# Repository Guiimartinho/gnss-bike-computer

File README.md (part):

<div align="center">

# GNSS Bike Computer

**Computador de bordo para ciclismo com GPS: segmentos do Strava em tempo real, percursos, altimetria por fusão de sensores e sensores sem fio. Portado do stravaV10 para Zephyr, do nRF52840 da myStravaB V3 para o nRF54LM20A de uma placa própria com GNSS de banda dupla e painel solar.**

</div>

O projeto leva para o nRF Connect SDK o **stravaV10**, firmware aberto de Vincent Gollé para a placa **myStravaB V3**: um aparelho em retrato com LCD de memória Sharp, GNSS MediaTek, barômetro, acelerômetro, medidor de bateria, microSD e rádio BLE + ANT+. O código original fica em [`legacy/`](legacy/) como referência de comportamento; o port em C puro sobre Zephyr fica em [`zephyr_app/`](zephyr_app/) e compila para o nRF54LM20 DK, para a placa do projeto (`gnssbike/nrf54lm20a/cpuapp`) e ainda para o nRF52840-DK, que saiu de uso. A próxima placa é própria, com o nRF54LM20A, GNSS de banda dupla, tela colorida e painéis solares na caixa que estendem a autonomia, sem sustentar o aparelho sozinhos; a especificação e a avaliação dos componentes estão em [`docs/`](docs/README.md).

> [!WARNING]
> O port **compila e passa nos testes de host, mas nunca rodou em placa nem nos DKs**. Segmentos, percursos, sensores BLE e ANT+, log no SD e a interface do legacy ainda não funcionam de ponta a ponta. A placa nova está roteada e com os arquivos de fábrica prontos, mas não foi fabricada: nenhum componente foi comprado nem medido. O estado de cada área está em [docs/10-status-do-port.md](docs/10-status-do-port.md).

## Índice

- [Visão geral](#visão-geral)
- [Placa nova](#placa-nova)
- [Funcionalidades](#funcionalidades)
- [Início rápido](#início-rápido)
- [Estrutura](#estrutura)
- [Documentação](#documentação)
- [Estado e próximos passos](#estado-e-próximos-passos)
- [Créditos e licenças](#créditos-e-licenças)

## Visão geral

```mermaid
flowchart LR
    subgraph DEV["myStravaB V3 · nRF52840"]
        MODEL["modelo<br/>altitude, potência,<br/>segmentos, percurso"]
        VUE["interface<br/>LCD LS027 + 3 botões"]
        LOG["log no microSD"]
    end
    GNSS["GNSS M10578-A3"] -->|NMEA| MODEL
    SENS["BME280 · FXOS8700 · STC3100"] -->|I2C| MODEL
    SENSORS["frequência cardíaca, cadência,<br/>potência, rolo"] -->|"ANT+ / BLE"| MODEL
    PHONE["celular<br/>Komoot, LNS"] -->|BLE| MODEL
    MODEL --> VUE
    MODEL --> LOG
    PC["PC"] <-->|"USB / stravaAP"| DEV
```

## Placa nova

<div align="center">

*A placa `gnssbike` roteada, 34 × 95 mm em 4 camadas, como sai na montagem da JDI, gerada por programa a partir dos documentos de `hardware_gnssbike/`.*

</div>

| | |
|---|---|
|  |  |
| *Frente: os dois conectores da tela, na borda esquerda: o `J402`, da luz da JDI (5 vias), e o `J401`, do sinal (10 vias), que serve às duas telas* | *Verso: o buzzer, o `J103` do painel solar e as ilhas do `J403`, que recebe a luz do Azumo na montagem da Sharp* |

| | |
|---|---|
|  |  |
| *A caixa proposta, 64 × 106 × 18,2 mm desde 2026-10-19, medida por um dry run próprio* | *Explodida: tampa com o display, teclas, módulos solares, porta do USB-C* |

A caixa foi desenhada em volta da placa real ([`hardware_gnssbike/caixa/`](hardware_gnssbike/caixa/README.md), decisões em [`hardware_gnssbike/04`](hardware_gnssbike/04-pcb-e-caixa.md#a-placa-de-hoje-dentro-da-caixa-do-conceito)); a placa, dimensionada pelo circuito e **não** pela caixa, tem 34 × 95 mm em 4 camadas, 6 módulos solares na faceta e nos chanfros laterais da caixa. A escolha de cada componente, com os números dos datasheets, está em [docs/15-avaliacao-componentes.md](docs/15-avaliacao-componentes.md); a lista de compras, validada peça a peça, em [docs/19-lista-de-compras.md](docs/19-lista-de-compras.md).

A placa existe como **arquivo de CAD**, gerado por programa e **roteado por
inteiro** em 2026-10-19: 138 componentes na montagem da JDI (146 na da
Sharp), 118 redes, 2.683 trechos de trilha e 769 vias. O DRC completo dá 0
itens desconectados e 0 erros, e as regras que as fichas dos componentes e a
IPC-2221B impõem, medidas uma a uma, dão 35 cumpridas, 2 com desvio aceito
pelo dono e conferência de bancada, e nenhuma violada
([dry run de 2026-10-19](hardware_gnssbike/09-dry-run-da-pcb.md#resultado-de-2026-10-19-com-o-roteamento-fechado)).
Os arquivos de fábrica da JLCPCB e as listas de compra da Mouser, da LCSC e
da DigiKey saem por script ([19](docs/19-lista-de-compras.md#compra-na-mouser)).
A caixa existe como proposta em volta da placa, medida por um dry run
próprio (12 regras cumpridas, nenhuma violada, 1 ainda sem medida). Nenhuma
placa foi fabricada, nada foi impresso e nenhum componente passou por
bancada. O esquemático, a placa, a caixa e como se confere cada etapa estão
em [hardware_gnssbike/](hardware_gnssbike/README.md).

```mermaid
flowchart LR
    MCU["MinewSemi ME54BS13<br/>nRF54LM20A, BLE e ANT+"]
    GNSS2["u-blox MAX-F10S<br/>L1 + L5, 46,8 mW"] -->|UART| MCU
    LCD2["JDI LPM027M128C de 8 cores, com luz,<br/>ou Sharp com a luz do Azumo"] ---|"SPI pelo J401"| MCU
    PWR["nPM1300, ADP5091, MAX17262<br/>USB-C e painel solar"] -.->|I2C| MCU
    SENS2["BMP585, BMI270,<br/>MMC5603NJ, OPT3001"] -->|I2C| MCU
    MEM["flash MX25R6435F<br/>8 MB, soldada"] ---|SPI| MCU
```

| Bloco | Escolha | Por quê |
|---|---|---|
| Carga | nPM1300 no USB-C, ADP5091 no painel, MAX17262 na célula | o painel carrega com o aparelho desligado e corte térmico próprio; o USB bloqueia a carga solar no hardware |
| GNSS | u-blox MAX-F10S, banda dupla L1 + L5, com o MAX-M10N-10B (só L1) no mesmo footprint | 1 m de CEP contra 1,5 m, e o código do L5 contra o multipercurso de prédio e mata. Custa autonomia: o aparelho gasta cerca de 58 mW e dura cerca de 115 h sem sol, e o painel devolve de 23 a 46 min por hora de sol em vez de cobrir o consumo. Com o M10N em LEAP seriam cerca de 21 mW e 310 h (estimativas) |
| Tela | JDI LPM027M128C de 8 cores, **com luz frontal integrada** (escolha do dono em 2026-09-23); de reserva, a Sharp LS027B7DH01A, nua ou como o módulo Azumo 11103-06, que traz a luz | as duas entram pelo mesmo conector de sinal, o `J401` (10 vias, contato dos dois lados), na borda esquerda da placa, e a luz tem conector próprio: o `J402` (5 vias), ao lado dele, na JDI, e o `J403` (4 vias, no verso) no Azumo. A montagem da Sharp leva também o boost de 5 V. O firmware atende as duas pelo mesmo driver, em retrato, com um tema para cada |
| USB e armazenamento | USB-C HRO TYPE-C-31-M-12 e flash MX25R6435F soldada | caixa sem tampas e sem cartão solto na vibração |

## Funcionalidades

| Funcionalidade | Legacy | Port |
|---|---|---|
| Segmentos do Strava com avanço contra o recorde | sim | lógica portada, sem carga de dados |
| Percurso com mapa e zoom | sim | parcial, não ligado |
| Altitude por Kalman de 3 estados, subida, inclinação | sim | portado com diferenças |
| Potência estimada | sim | fórmula diferente |
| Sensores ANT+ (FC, velocidade e cadência, rolo FE-C) | sim | a pilha do add-on `sdk-ant` compila com o NCS v3.3.0 (`ANT=1`) e o firmware abre canal escravo; **nenhum canal abre de fato**, porque os perfis ficam fora do repositório e `GNSS_ANT_*_DEV_TYPE` valem 0 |
| BLE (potência, posição do celular, Komoot) | sim | parcial |
| Zonas de potência, suffer score, variabilidade da FC | sim | portados e testados, sem dados reais |
| Log no microSD e download pelo PC | sim | FatFs de verdade, gravado pelo serviço de armazenamento; não testado com cartão |
| USB serial e mass storage | sim | serviço `usb` no build (CDC dos comandos e o disco do ciclista); não testada com cabo |
| Telas em retrato, menu, notificações, botões | sim | LVGL no firmware com driver próprio da tela, 44 quadros testados no PC; nunca vistos num painel |

## Início rápido

**Pré-requisitos** (Windows): nRF Connect SDK v3.3.0 em `C:\ncs` com o toolchain `936afb6332`, SEGGER J-Link, nRF54LM20 DK (o nRF52840-DK ainda compila, mas saiu de uso). Para o ANT, o add-on `sdk-ant` em `C:\ncs\sdk-ant`, depois de aceitar o acordo ANT+ ([07](docs/07-radio-ant-ble.md#ant-no-ncs-v330)). Para os testes de host: MinGW-w64 GCC, CMake e Ninja. Detalhes em [docs/03-ambiente-build.md](docs/03-ambiente-build.md).

Código: [github.com/Guiimartinho/gnss-bike-computer](https://github.com/Guiimartinho/gnss-bike-computer) (`git clone https://github.com/Guiimartinho/gnss-bike-computer.git`).

```sh
# Git Bash, na raiz do repositório
bash tools/fw/fw.sh build          # compila o zephyr_app (sysbuild) para o nRF54LM20 DK
bash tools/fw/fw.sh flash          # grava no DK pelo J-Link
BOARD=gnssbike/nrf54lm20a/cpuapp BUILD_DIR=zephyr_app/build_custom bash tools/fw/fw.sh build   # a placa do projeto
ANT=1 bash tools/fw/fw.sh build pristine   # com a pilha ANT do sdk-ant
bash tools/fw/host_tests.sh        # 53 conjuntos, 714 casos
python tools/ui/render_screens.py  # desenha os 44 quadros no PC (docs/telas)
python tools/docs/mermaid_check.py # valida os diagramas da documentação
```

No `cmd` ou com duplo clique: `build.bat`, `flash.bat`, `recover.bat`, `serial.bat COMx`.

O CI (`.github/workflows/ci.yml`) está **desligado**: só roda à mão, pela aba Actions do GitHub ([detalhes](docs/03-ambiente-build.md#ci)).

## Estrutura

```mermaid
flowchart TB
    ROOT["gnss_bike_computer/"]
    ROOT --> ZA["zephyr_app/<br/>port Zephyr: src, include, boards, modules, tests/host"]
    ROOT --> LEG["legacy/<br/>stravaV10 original (referência)"]
    ROOT --> LIB["libraries/<br/>bibliotecas do legacy"]
    ROOT --> TOOLS["tools/<br/>fw e docs do projeto · TDD, zpm, MMD, jumper do legacy"]
    ROOT --> HW["hardware/<br/>Eagle da myStravaB V3 (Gerbers da V2)"]
    ROOT --> HWN["hardware_gnssbike/<br/>a placa nova: docs 01 a 12, cad (KiCad e geradores),<br/>esquematico, placa, caixa (PDF, STL, dry run), datasheets,<br/>fabricacao (gerada, fora do git)"]
    ROOT --> DOCS["docs/<br/>documentação numerada, img (telas, hardware), historico"]
    ROOT --> AI["CLAUDE.md · AGENTS.md · .claude/skills/ · .claude/contexto/"]
    ROOT --> BAT["build.bat · flash.bat · recover.bat · serial.bat"]
```

## Documentação

| Documento | Assunto |
|---|---|
| [01 · Visão geral](docs/01-visao-geral.md) | produto, modos, legacy e port |
| [02 · Hardware](docs/02-hardware.md) | placa, pinagem, alimentação, alvo no DK |
| [03 · Ambiente e build](docs/03-ambiente-build.md) | NCS v3.3.0, scripts, gravação, problemas conhecidos |
| [04 · Arquitetura do legacy](docs/04-arquitetura-legacy.md) | tasks, modos, glossário |
| [05 · Arquitetura do port](docs/05-arquitetura-zephyr.md) | threads, fluxo de dados, pilhas, devicetree |
| [06 · Algoritmos](docs/06-algoritmos.md) | fórmulas e constantes, legacy × port |
| [07 · Rádio](docs/07-radio-ant-ble.md) | ANT+, BLE, stravaAP, Komoot |
| [08 · Interface](docs/08-interface.md) | telas, menus, botões |
| [09 · Armazenamento e USB](docs/09-armazenamento-usb.md) | formatos de arquivo, SD, USB |
| [10 · Status do port](docs/10-status-do-port.md) | matriz, correções, defeitos, roteiro, decisões |
| [11 · Qualidade e MISRA](docs/11-qualidade-misra.md) | regras e análise estática |
| [12 · Ferramentas e testes](docs/12-ferramentas-testes.md) | testes de host, simulador do legacy, licenças |
| [13 · Placa nova](docs/13-placa-nova.md) | proposta de hardware da placa própria |
| [14 · Hardware da placa nova](docs/14-hardware-placa-nova.md) | especificação técnica: alimentação, lista de materiais, pinos, PCB |
| [15 · Avaliação dos componentes](docs/15-avaliacao-componentes.md) | escolha de cada componente da placa nova, com números de datasheet |
| [16 · Arquitetura do firmware](docs/16-arquitetura-firmware.md) | arquitetura-alvo e máquinas de estado para a placa nova |
| [17 · Dispositivos BLE e ANT+](docs/17-dispositivos-ble-ant.md) | catálogo de sensores e acessórios, prioridades e limites do rádio |
| [18 · Interface e telas](docs/18-interface-telas.md) | interface LVGL da placa nova: todas as telas, desenhadas e testadas no PC, em 8 cores e em preto e branco |
| [19 · Lista de compras](docs/19-lista-de-compras.md) | peças validadas em duas passagens, trocas, correções de integração, e o pedido dividido entre Mouser, LCSC e DigiKey |
| [Hardware da placa nova](hardware_gnssbike/README.md) | o esquemático folha a folha, os cálculos, a lista de nós, a placa e a caixa, os conectores, o layout e os dois dry runs; o CAD em [`cad/`](hardware_gnssbike/cad/README.md), a caixa em [`caixa/`](hardware_gnssbike/caixa/README.md), os PDF em [`esquematico/`](hardware_gnssbike/esquematico/) e [`placa/`](hardware_gnssbike/placa/) |
| [CHANGELOG](CHANGELOG.md) | histórico de mudanças |

## Estado e próximos passos

- **Feito em 2026-09-18:** build no NCS v3.3.0 com sysbuild; correção de 13 defeitos críticos (estouro de pilha no Kalman, GPS e modelo dentro de ISR, corrupção de memória no log, botões e pinos do GPS invertidos, conflitos de pinos com o DK); testes de host; documentação e contexto para assistentes de IA.
- **Fase 1 do roteiro:** a base da arquitetura nova (serviços com thread própria, eventos no zbus, máquinas de sistema e de modo no SMF, watchdog por serviço, desligamento automático do legacy), feita em 2026-09-19.
- **Novos alvos e rádio:** o port compila para o nRF54LM20 DK, e a pilha ANT do add-on `sdk-ant` v2.1.1 compila sobre o NCS v3.3.0 nos dois DKs (`ANT=1`); nada disso foi testado em placa.
- **Interface:** os 44 quadros em LVGL, testadas no PC, rodam no firmware desde 2026-09-19 com um driver próprio da tela (JDI LPM027M128B em 8 cores ou Sharp em preto e branco, em retrato), teclas com toque longo e a máquina da luz; nunca vistas num painel.
- **Placa nova:** desenho do aparelho, especificação ([14](docs/14-hardware-placa-nova.md)) e avaliação dos componentes ([15](docs/15-avaliacao-componentes.md)). Os testes de bancada da carga dupla, do GNSS (C/N0 por banda e isolamento da antena contra o rádio de 2,4 GHz), da coexistência dos rádios e do display ficam para o protótipo.
- **Hardware da placa nova (2026-09-23 a 10-20):** o esquemático em sete folhas, revisado em 2026-10-18; a placa de 34 × 95 mm colocada por programa e roteada por inteiro em 2026-10-19, que aceita a JDI ou a Sharp; o desenho de montagem, o manual e o chicote solar; os dry runs da placa (as regras das fichas e da IPC-2221 medidas no arquivo) e da caixa (a caixa medida contra a placa); a caixa de 64 × 106 × 18,2 com STL para a primeira prova; os arquivos de fábrica da JLCPCB e as listas de compra. Nada fabricado, nada impresso, nenhum componente na bancada; o que falta antes de mandar fabricar está em [`hardware_gnssbike/README.md`](hardware_gnssbike/README.md#antes-de-mandar-fabricar).
- **Decidido:** ANT+ e BLE juntos (os equipamentos externos falam ANT+) e placa própria com o nRF54LM20A. Decisões e pendências em [docs/10-status-do-port.md](docs/10-status-do-port.md#decisões-do-dono).
- **Próximo:** as confirmações que faltam antes de mandar fabricar (o mapa de pads do módulo num exemplar real, o domínio de tensão do nPM1300, a pinagem da bateria), a compra das peças e a primeira prova impressa da caixa; depois, os testes de bancada da placa nova (carga dupla, isolamento entre as antenas, o display sobre a antena GNSS); no firmware, fidelidade dos algoritmos, armazenamento, rádio e interface. Roteiro em [docs/10-status-do-port.md](docs/10-status-do-port.md#roteiro).

## Créditos e licenças

- **stravaV10** e **myStravaB**: Vincent Gollé ([vincent290587/stravaV10](https://github.com/vincent290587/stravaV10)), licenciado sob **Creative Commons Atribuição-NãoComercial 4.0 (CC BY-NC 4.0)**. O port deriva desse código; ver [`legacy/README.md`](legacy/README.md).
- Bibliotecas de terceiros em `libraries/` e `tools/` mantêm suas licenças (BSD, LGPL-2.1, GPL-2.0, Nordic, SEGGER): tabela em [docs/12-ferramentas-testes.md](docs/12-ferramentas-testes.md#bibliotecas-e-licenças).
- O add-on `sdk-ant` e o material ANT+ não fazem parte do repositório: o ANT+ Adopter Agreement proíbe redistribuir ([07](docs/07-radio-ant-ble.md#decisão-ant-e-ble)).
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
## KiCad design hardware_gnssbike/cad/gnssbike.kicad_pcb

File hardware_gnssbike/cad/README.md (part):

# Projeto KiCad da placa

Este diretório é o projeto de CAD do GNSS Bike Computer: **esquemático
hierárquico em sete folhas** e **placa com as 166 peças posicionadas e
roteadas**, em KiCad 8, gerados a partir dos documentos de
[`hardware_gnssbike/`](../README.md) e conferidos contra eles por programa.

> [!WARNING]
> **Nada aqui foi fabricado, montado ou medido.** Não existe placa, não existe
> protótipo e nenhum número desta página saiu de bancada. O roteamento é feito
> por programa e está **completo desde 2026-10-19** (0 itens desconectados e 0
> erros no DRC completo), com rotina própria para as linhas de RF; nenhuma
> placa de verdade o conferiu.

## O que abrir

| Arquivo | O que é |
|---|---|
| `gnssbike.kicad_pro` | o projeto; **abra este** no KiCad |
| `gnssbike.kicad_sch` | folha raiz: o diagrama de blocos |
| `folha1-energia.kicad_sch` … `folha6-interface.kicad_sch` | as seis folhas |
| `gnssbike.kicad_pcb` | a placa |
| `gnssbike.kicad_dru` | as duas regras locais de folga |
| `zonas.dxf`, `contorno-r3.dxf`, `contorno-r4.dxf` | as zonas e o contorno da placa em DXF, gerados pelo `make_dxf.py` (entradas da placa, não saídas) |

O que se **lê** sai daqui para as pastas do assunto (reorganização de 2026-09-26): o esquemático em PDF para [`../esquematico/`](../esquematico/), a placa em PDF e SVG e o desenho de montagem para [`../placa/`](../placa/), a proposta de caixa (PDF, STL e os dois scripts dela) para [`../caixa/`](../caixa/README.md), e as vistas 3D da placa e da caixa para [`../../docs/img/hardware/`](../../docs/img/hardware/). A tabela de [`../README.md`](../README.md#o-cad-e-o-que-sai-dele) lista cada arquivo. O `gnssbike.glb` que o `kicad-cli` exporta fica aqui e fora do git (45 MB, regenerado quando a placa muda).

## O esquemático

```mermaid
flowchart TB
    RAIZ["folha raiz · A3<br/>diagrama de blocos<br/>as linhas entre as folhas"]
    RAIZ --> F1["1 Energia · A3<br/>79 posicoes em 6 blocos"]
    RAIZ --> F2["2 MCU e depuracao · A4<br/>14 posicoes em 2 blocos"]
    RAIZ --> F3["3 GNSS · A4<br/>13 posicoes em 2 blocos"]
    RAIZ --> F4["4 Display e luz · A4<br/>15 posicoes em 2 blocos"]
    RAIZ --> F5["5 Memoria e sensores · A4<br/>18 posicoes em 5 blocos"]
    RAIZ --> F6["6 Interface · A4<br/>23 posicoes em 3 blocos"]
```

### Desenhado por bloco funcional, desde 2026-09-26

Até esse dia cada folha era a lista de nós desenhada em fios: as peças numa
grade por ordem de ligação e o roteador de labirinto puxando um fio de cada
pino até o outro extremo, fosse ele do outro lado da página. O dono pediu o
padrão industrial — ligações e rótulos, A4 ou A3, peças certas, fácil de
ler, os circuitos subdivididos em caixas tracejadas —, e o `blocos.py` é
isso:

| Regra | Como | De onde vem |
|---|---|---|
| Cada folha é uma fila de **blocos funcionais**, na ordem em que o sinal flui, cada um numa **caixa tracejada com título** | a tabela `BLOCOS` de `blocos.py` diz as âncoras de cada bloco (o CI ou o conector); os passivos seguem `make_pcb.DECOPLA` e `JUNTO` (as tabelas que já dizem de quem é cada capacitor na placa), depois `sheets.SEGUE`, depois a lista de nós sem os trilhos (o vizinho mais próximo por saltos) | SparkFun, "How to read a schematic": "truly expansive schematics should be split into functional blocks", "following the flow of circuit from input to output" |
| Dentro do bloco, o passivo fica **ao lado do pino que serve**, do lado para onde o pino aponta; o desacoplamento vai numa **prateleira** sob o CI | `_colocar_bloco()`: a âncora no meio, cada membro a dois passos da ponta do pino que compartilha com ela, empurrado para fora até caber sem sobrepor nem encostar ponta de outra rede; o que só toca trilho vai para a prateleira, que quebra linha na largura da âncora | prática corrente; a razão é o roteador: um fio curto sempre passa |
| Um passivo de dois terminais é **espelhado** quando o pino que serve ao CI é o de trás, e **posto em pé** (90° ou 270°) na prateleira e quando é pull-up ou pull-down de uma linha rotulada | `Part.espelho` e `Part.rotacao`. A **biblioteca** guarda sempre o desenho base (`pin_base()`); a instância leva o giro e o espelho, e `pin_local()` diz onde as pontas ficam depois deles. **Medido** no KiCad 8 em 2026-09-26, com treze resistores de biblioteca base e um rótulo colado em cada ponta (`kicad-cli sch export netlist`): `(mirror y)` troca esquerda por direita, `(mirror x)` troca cima por baixo; `(at x y 90)` manda o pino da esquerda para **baixo**, `270` para cima; a rotação vem antes do espelho. E, pelo `sch export pdf`: a justificação do campo de texto também é transformada (sob `(mirror y)` "left" imprime como "right"; a 90° trocam os dois eixos; a 270° nada), e `instance()` escreve a justificação que **renderiza** como a pedida | a primeira "medição" saiu invertida porque foi feita através do gerador, que escrevia a biblioteca já espelhada e ainda punha o `(mirror ...)` na instância: transformação duas vezes. Foi assim que todos os capacitores em pé saíram com as duas pontas no ar em 2026-09-26 |
| Alimentação e terra por **símbolo**, apontando **para longe do pino**: deitado ao longo da linha num pino lateral (seta ou barras para fora, o nome na linha, depois delas), em pé num pino de cima ou de baixo; pinos vizinhos do mesmo trilho no mesmo lado, ou os topos de uma fileira de capacitores em pé, ganham **um fio pela ponta deles e um símbolo só** | `PowerPort.sentido` (U, D, L, R); o nome fica a 3,3 mm do ponto, entre duas linhas de pino. Em pé num pino lateral, o símbolo punha a seta na linha de cima e o nome na seguinte. O fio da corrida é um por par de vizinhos: "wires connect with other wires or pins only if their ends coincide exactly" — um pino no meio de um fio comprido **não** está nele; e cada célula do fio é marcada no roteador (só as pontas e o meio deixavam um rótulo de outra rede pousar no meio dele) | manual do Eeschema 8; prática corrente nos esquemáticos densos |
| A **prateleira** é uma fileira de capacitores em pé, agrupados por trilho, com passo de 12,7 mm; o trilho corre pelos topos e o terra pelos pés, um símbolo por fileira; os pontos de teste ficam em pé com o pad pendurado da linha | `_colocar_bloco()` (prateleira), `PASSO_PRATELEIRA`, `ENTRE_LINHAS_PRATELEIRA`, `LARGURA_PRATELEIRA`; a referência e o valor à direita da peça, escritos a 90° (o KiCad soma o giro da instância ao ângulo do campo) | é como toda folha de desacoplamento é desenhada |
| Pull-up ou pull-down de uma linha que **sai do bloco** fica **em pé, depois do rótulo**; quando a linha segue para outra âncora (os contatos do FPC ao painel), fica **fora do corredor** das linhas, acima (trilho) ou abaixo (terra), e o roteador desce um fio até a linha cruzando as outras em ângulo reto | `_colocar_bloco()`: `em_pe`, distância pelo comprimento do maior rótulo vizinho (`GAP_ROTULO` no mínimo). Deitado na linha, ficava debaixo do texto do rótulo; em pé sobre a linha, era um muro para as linhas ao lado | é como uma fileira de pull-ups é desenhada |
| Os **rótulos têm o lugar reservado antes** das peças: cada pino de âncora cuja rede sai do bloco ganha um retângulo (toco de dois passos, texto, pentágono) que nenhum corpo nem texto de membro toma; e o que cada peça ocupa é testado como retângulos **separados** (corpo com pinos, cada texto), nunca uma caixa envolvente só | `retangulos` em `_colocar_bloco()`; `Part.caixas_de_texto()`. Uma caixa só em volta do conector FPC e do seu valor de 26 mm murava todas as linhas à direita dele | — |
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
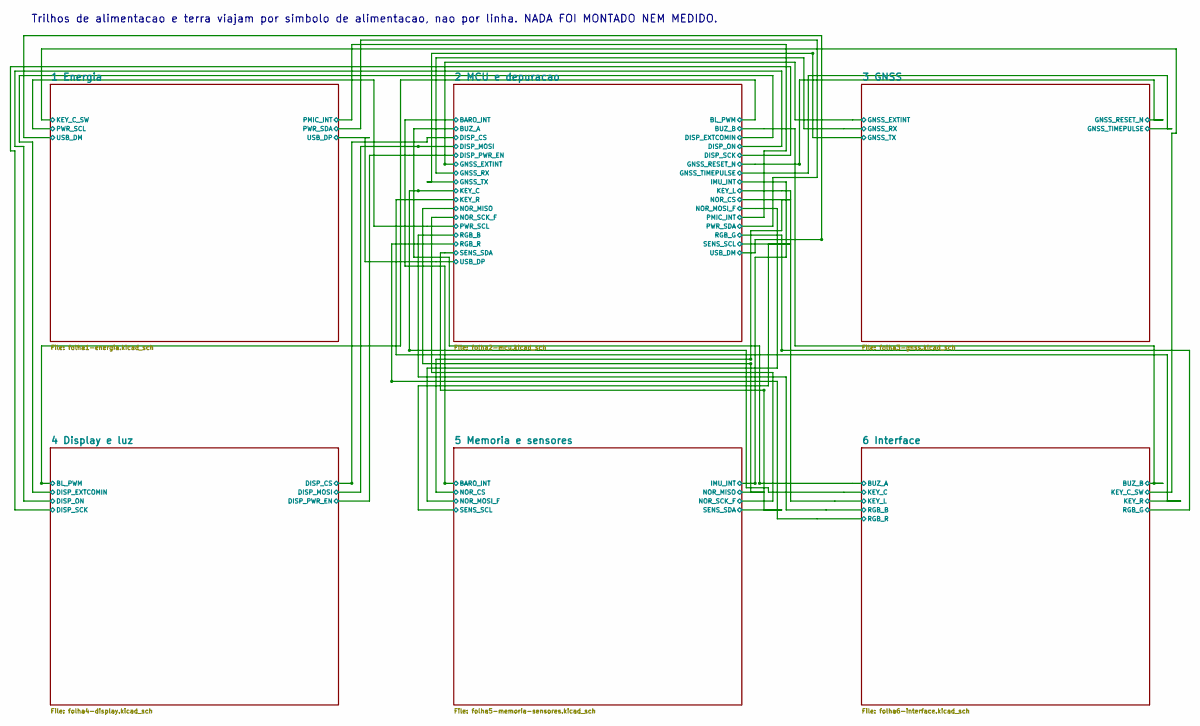
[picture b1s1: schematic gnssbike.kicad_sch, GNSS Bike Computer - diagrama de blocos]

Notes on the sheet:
Trilhos de alimentacao e terra viajam por simbolo de alimentacao, nao por linha. NADA FOI MONTADO NEM MEDIDO.

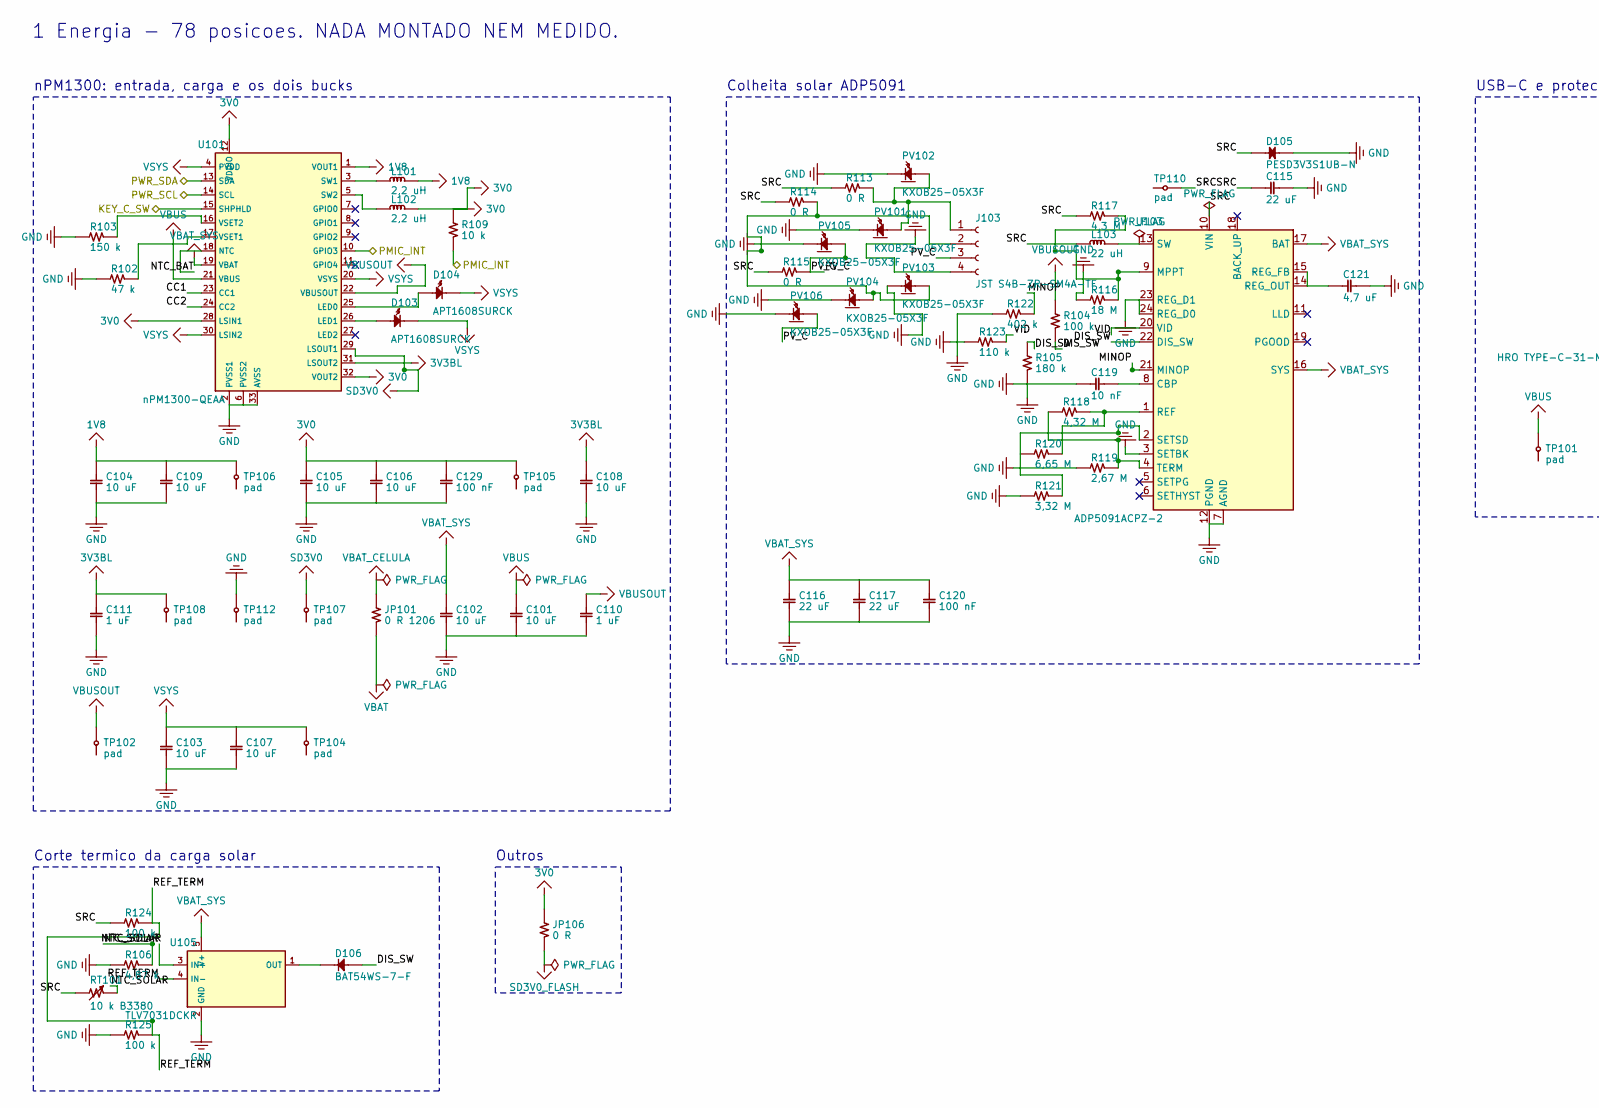
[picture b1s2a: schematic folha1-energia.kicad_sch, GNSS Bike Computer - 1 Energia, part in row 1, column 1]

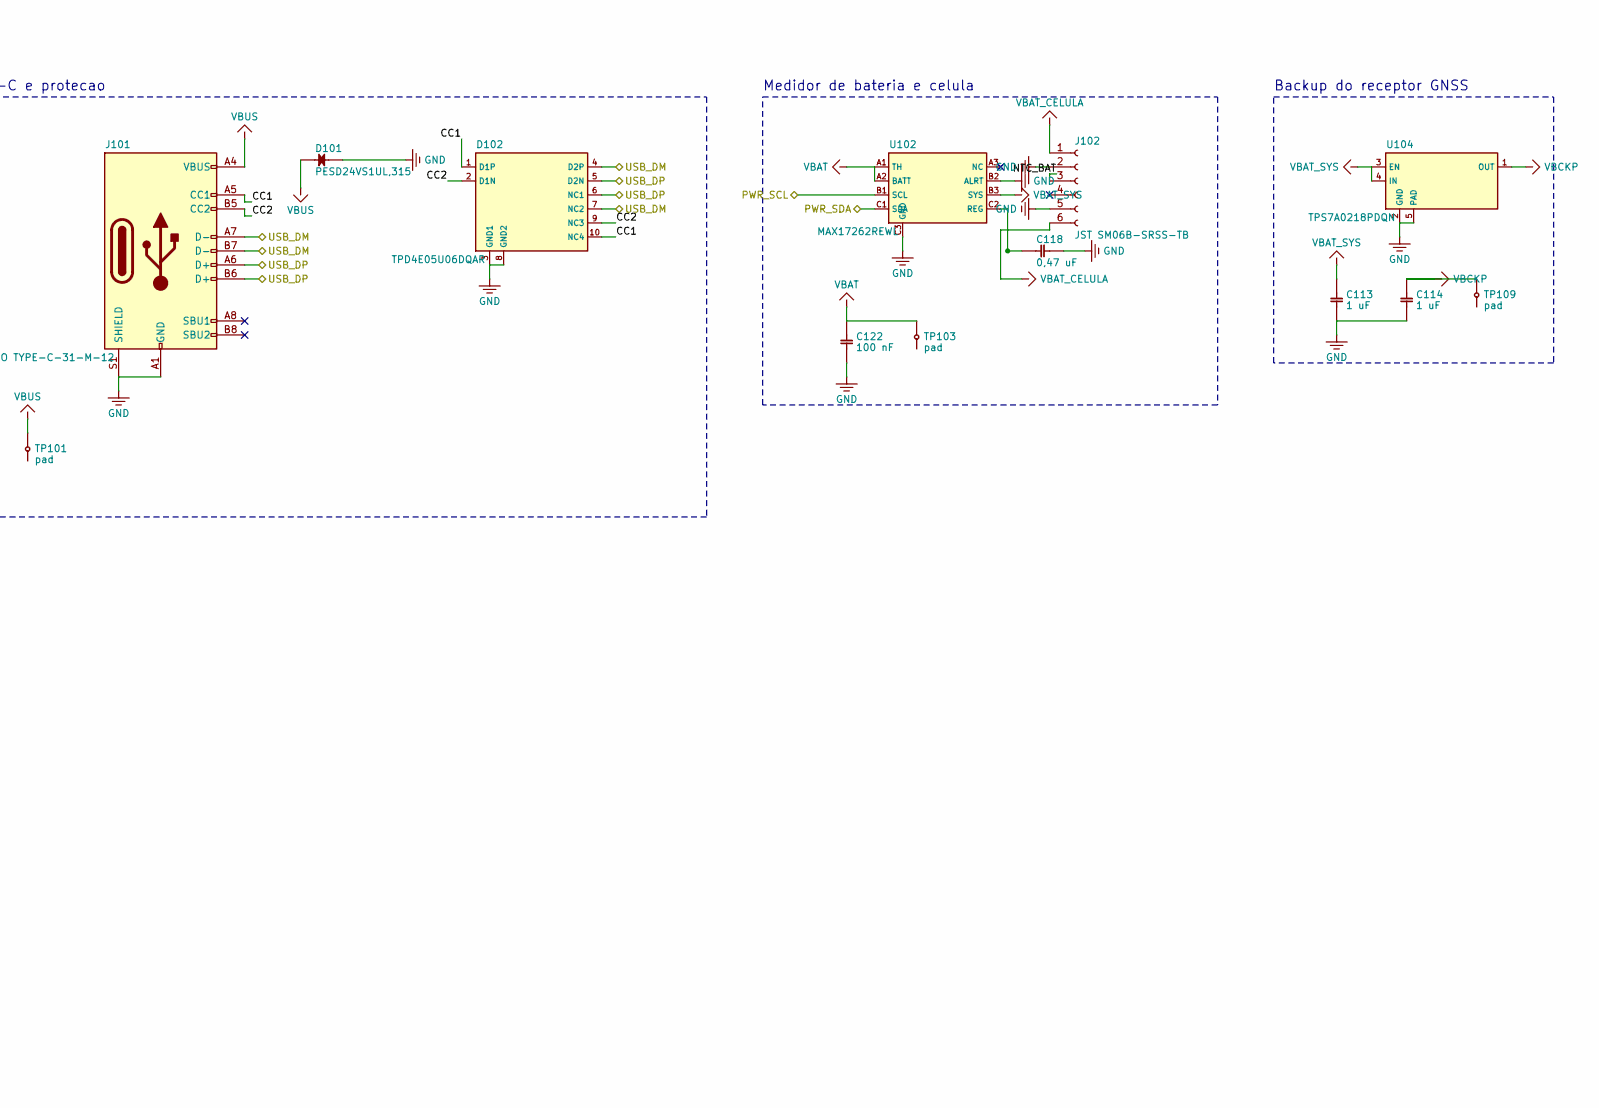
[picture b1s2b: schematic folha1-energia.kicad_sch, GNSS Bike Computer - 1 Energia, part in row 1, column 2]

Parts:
C101, C102, C103, C104, C105, C106, C107, C108, C109: 10 uF; C_0603_1608Metric
C110, C111, C113, C114: 1 uF; C_0402_1005Metric
C115, C116: 22 uF; C_0402_1005Metric
C117: 22 uF; C_0603_1608Metric
C118: 0,47 uF; C_0402_1005Metric
C119: 10 nF; R_0402_1005Metric
C120: 100 nF; R_0402_1005Metric
C121: 4,7 uF; R_0402_1005Metric
C122, C129: 100 nF; C_0603_1608Metric
D101: PESD24VS1UL,315; D_SOD-882
D102: TPD4E05U06DQAR; TPD4E05U06_USON-10_1x2.5mm_P0.5mm
D103, D104: APT1608SURCK; LED_0603_1608Metric
D105: PESD3V3S1UB-N; D_SOD-523
D106: BAT54WS-7-F; D_SOD-323
J101: HRO TYPE-C-31-M-12; USB_C_Receptacle_HRO_TYPE-C-31-M-12
J102: JST SM06B-SRSS-TB; JST_SH_SM06B-SRSS-TB_1x06-1MP_P1.00mm_Horizontal
J103: JST S4B-ZR-SM4A-TF; JST_ZH_S4B-ZR-SM4A-TF_1x04-1MP_P1.50mm_Horizontal
JP101: 0 R 1206; R_1206_3216Metric
JP106: 0 R; R_0402_1005Metric
L101, L102: 2,2 uH; L_Murata_DFE201610P
L103: 22 uH; L_1008_2520Metric
PV101, PV102, PV103, PV104, PV105, PV106: KXOB25-05X3F
R102: 47 k; R_0402_1005Metric
R103: 150 k; R_0402_1005Metric
R104, R124, R125: 100 k; R_0402_1005Metric
R105: 180 k; R_0402_1005Metric
R106: 4,87 k; R_0402_1005Metric
R109: 10 k; R_0402_1005Metric
R113, R114, R115: 0 R; R_0402_1005Metric
R116: 18 M; R_0402_1005Metric
R117: 4,3 M; R_0402_1005Metric
R118: 4,32 M; R_0402_1005Metric
R119: 2,67 M; R_0402_1005Metric
R120: 6,65 M; R_0402_1005Metric
R121: 3,32 M; R_0402_1005Metric
R122: 402 k; R_0402_1005Metric
R123: 110 k; R_0402_1005Metric
RT101: 10 k B3380; R_0402_1005Metric
TP101, TP102, TP103, TP104, TP105, TP106, TP107, TP108, TP109, TP110, TP112: pad; TestPoint_Pad_D1.0mm
U101: nPM1300-QEAA; QFN-32-1EP_5x5mm_P0.5mm_EP3.45x3.45mm
U102: MAX17262REWL; MAX17262_WLP-9_1.4x1.4mm_P0.4mm
U103: ADP5091ACPZ-2; LFCSP-24-1EP_4x4mm_P0.5mm_EP2.3x2.3mm
U104: TPS7A0218PDQN; Texas_X2SON-4_1x1mm_P0.65mm
U105: TLV7031DCKR; SOT-353_SC-70-5

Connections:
1V8: C104.1, C109.1, L101.2, TP106.1, U101.1 (VOUT1)
3V0: C105.1, C106.1, C129.1, JP106.1, L102.2, R109.1, TP105.1, U101.12 (VDDIO), U101.28 (LSIN1), U101.32 (VOUT2); also elsewhere on the board
3V3BL: C108.1, C111.1, TP108.1, U101.31 (LSOUT2); also elsewhere on the board
ADP_REF: R118.1, R120.1, U103.1 (REF)
BUCK1_SW: L101.1, U101.3 (SW1)
BUCK2_SW: L102.1, U101.5 (SW2)
CBP: C119.1, U103.8 (CBP)
CC1: D102.1 (D1P), D102.10 (NC4), J101.A5 (CC1), U101.23 (CC1)
CC2: D102.2 (D1N), D102.9 (NC3), J101.B5 (CC2), U101.24 (CC2)
DIS_SW: D106.1 (K), R104.2, R105.1, U103.22 (DIS_SW)
GND: C101.2, C102.2, C103.2, C104.2, C105.2, C106.2, C107.2, C108.2, C109.2, C110.2, C111.2, C113.2, C114.2, C115.2, C116.2, C117.2, C118.2, C119.2, C120.2, C121.2, C122.2, C129.2, D101.2 (GND), D102.3 (GND1), D102.8 (GND2), D105.2 (GND), J101.A1 (GND), J101.A12 (GND), J101.B1 (GND), J101.B12 (GND), J101.S1 (SHIELD), J102.2, J102.5, J103.4, PV101.2 (N), PV102.2 (N), PV103.2 (N), PV104.2 (N), PV105.2 (N), PV106.2 (N), R102.2, R103.2, R105.2, R106.2, R116.2, R119.2, R121.2, R122.2, R123.2, R125.2, TP112.1, U101.2 (PVSS1), U101.6 (PVSS2), U101.33 (AVSS), U102.B2 (ALRT), U102.C3 (GND), U103.3 (SETBK), U103.7 (AGND), U103.12 (PGND), U103.23 (REG_D1), U103.24 (REG_D0), U103.25 (AGND), U104.2 (GND), U104.5 (PAD), U105.2 (GND); also elsewhere on the board
KEY_C_SW: U101.15 (SHPHLD); also elsewhere on the board
LED_CHG: D103.1 (K), U101.26 (LED1)
LED_ERR: D104.1 (K), U101.25 (LED0)
MINOP: R122.1, U103.21 (MINOP)
MPPT: R116.1, R117.2, U103.9 (MPPT)
NTC_BAT: J102.3, U101.18 (NTC)
NTC_SOLAR: R106.1, RT101.2, U105.3 (IN+)
PMIC_INT: R109.2, U101.10 (GPIO3); also elsewhere on the board
PV_A: J103.1, PV101.1, PV102.1, R113.1
PV_B: J103.2, PV103.1, PV104.1, R114.1
PV_C: J103.3, PV105.1, PV106.1, R115.1
PWR_SCL: U101.14 (SCL), U102.B1 (SCL); also elsewhere on the board
PWR_SDA: U101.13 (SDA), U102.C1 (SDA); also elsewhere on the board
REF_TERM: R124.2, R125.1, U105.4 (IN-)
REG_GAUGE: C118.1, U102.C2 (REG)
REG_OUT: C121.1, U103.14 (REG_OUT), U103.15 (REG_FB)
RVSET1: R102.1, U101.17 (VSET1)
RVSET2: R103.1, U101.16 (VSET2)
SD3V0: TP107.1, U101.29 (LSOUT1)
SD3V0_FLASH: JP106.2; also elsewhere on the board
SETSD: R120.2, R121.1, U103.2 (SETSD)
SRC: C115.1, D105.1 (IO), L103.1, R113.2, R114.2, R115.2, R117.1, R124.1, RT101.1, TP110.1, U103.10 (VIN)
SW_DCDC: L103.2, U103.13 (SW)
TERM: R118.2, R119.1, U103.4 (TERM)
TERM_QUENTE: D106.2 (A), U105.1 (OUT)
USB_DM: D102.4 (D2P), D102.7 (NC2), J101.A7 (D-), J101.B7 (D-); also elsewhere on the board
USB_DP: D102.5 (D2N), D102.6 (NC1), J101.A6 (D+), J101.B6 (D+); also elsewhere on the board
VBAT: C122.1, JP101.2, TP103.1, U102.A1 (TH), U102.A2 (BATT)
VBAT_CELULA: J102.1, J102.6, JP101.1
VBAT_SYS: C102.1, C113.1, C116.1, C117.1, C120.1, U101.19 (VBAT), U102.B3 (SYS), U103.16 (SYS), U103.17 (BAT), U104.3 (EN), U104.4 (IN), U105.5 (V+)
VBCKP: C114.1, TP109.1, U104.1 (OUT); also elsewhere on the board
VBUS: C101.1, D101.1 (IO), J101.A4 (VBUS), J101.A9 (VBUS), J101.B4 (VBUS), J101.B9 (VBUS), TP101.1, U101.21 (VBUS)
VBUSOUT: C110.1, R104.1, TP102.1, U101.22 (VBUSOUT); also elsewhere on the board
VID: R123.1, U103.20 (VID)
VSYS: C103.1, C107.1, D103.2 (A), D104.2 (A), TP104.1, U101.4 (PVDD), U101.20 (VSYS), U101.30 (LSIN2); also elsewhere on the board

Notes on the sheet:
USB-C e protecao
nPM1300: entrada, carga e os dois bucks
Medidor de bateria e celula
Backup do receptor GNSS
Colheita solar ADP5091
Corte termico da carga solar
Outros
1 Energia - 78 posicoes. NADA MONTADO NEM MEDIDO.

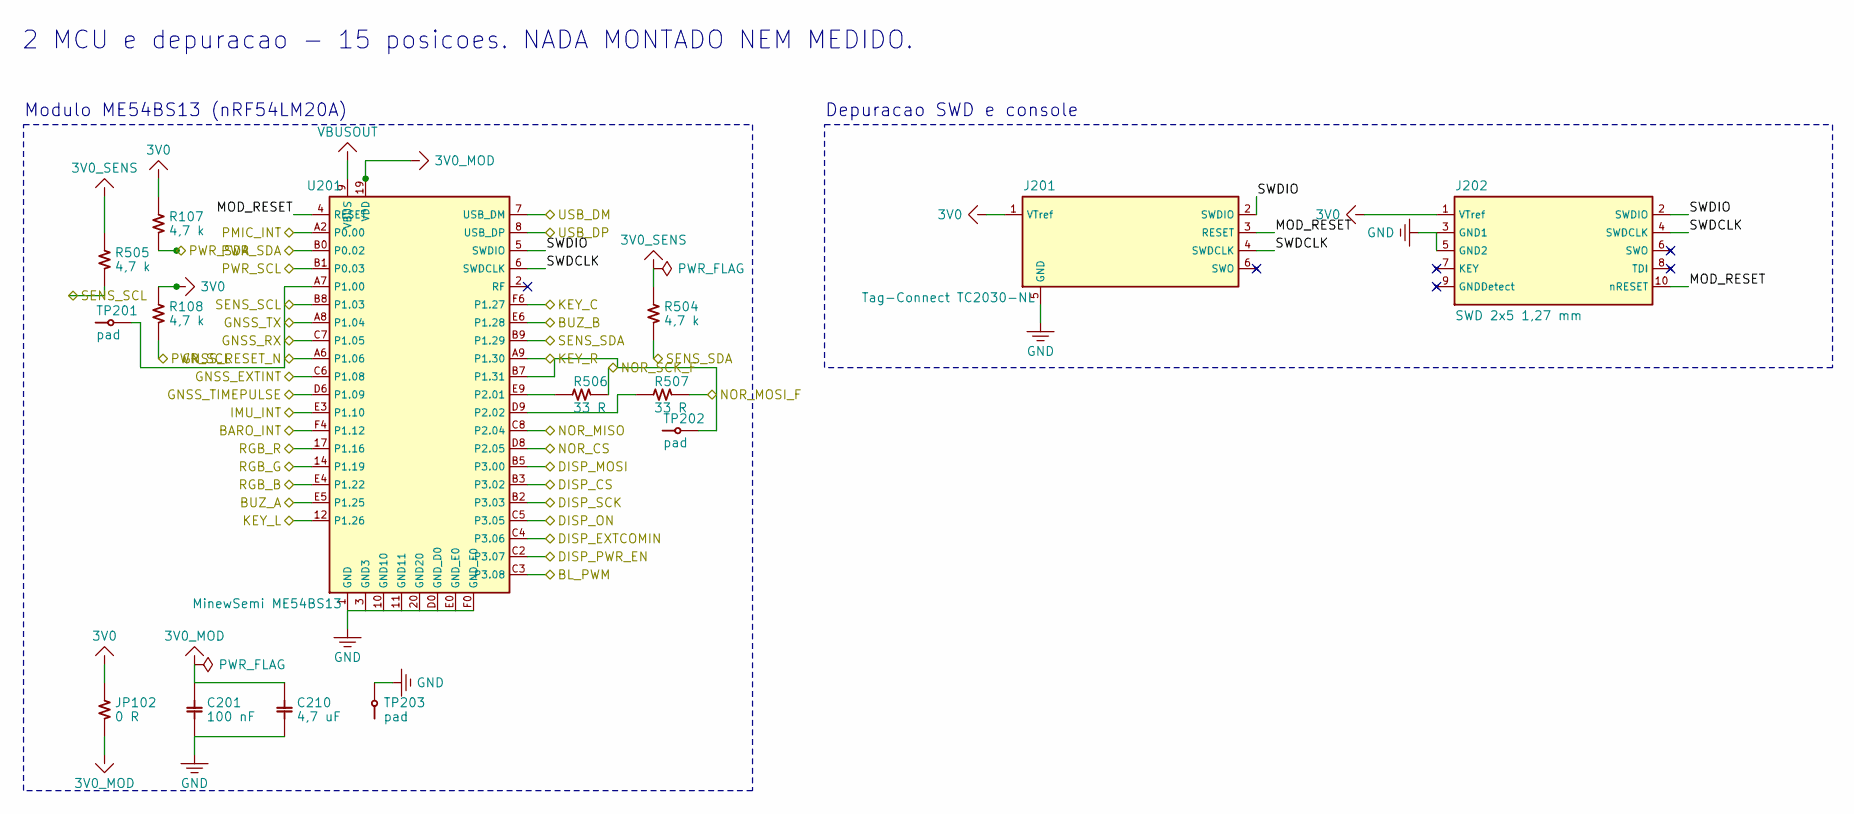
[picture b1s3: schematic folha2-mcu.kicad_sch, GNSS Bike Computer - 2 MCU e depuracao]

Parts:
C201: 100 nF; C_0402_1005Metric
C210: 4,7 uF; C_0603_1608Metric
J201: Tag-Connect TC2030-NL; Tag-Connect_TC2030-IDC-NL_2x03_P1.27mm_Vertical
J202: SWD 2x5 1,27 mm; PinHeader_2x05_P1.27mm_Vertical_SMD
JP102: 0 R; R_0402_1005Metric
R107, R108, R504, R505: 4,7 k; R_0402_1005Metric
R506, R507: 33 R; R_0402_1005Metric
TP201, TP202, TP203: pad; TestPoint_Pad_D1.0mm
U201: MinewSemi ME54BS13; MinewSemi_ME54BS13_16.5x12mm

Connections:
3V0: J201.1 (VTref), J202.1 (VTref), JP102.1, R107.1, R108.1; also elsewhere on the board
3V0_MOD: C201.1, C210.1, JP102.2, U201.19 (VDD)
3V0_SENS: R504.1, R505.1; also elsewhere on the board
BARO_INT: U201.F4 (P1.12); also elsewhere on the board
BL_PWM: U201.C3 (P3.08); also elsewhere on the board
BUZ_A: U201.E5 (P1.25); also elsewhere on the board
BUZ_B: U201.E6 (P1.28); also elsewhere on the board
CON_RX: TP202.1, U201.B7 (P1.31)
CON_TX: TP201.1, U201.A7 (P1.00)
DISP_CS: U201.B3 (P3.02); also elsewhere on the board
DISP_ON: U201.C5 (P3.05); also elsewhere on the board
DISP_PWR_EN: U201.C2 (P3.07); also elsewhere on the board
FPC_EXTCOMIN: U201.C4 (P3.06); also elsewhere on the board
FPC_SCLK: U201.B2 (P3.03); also elsewhere on the board
FPC_SI: U201.B5 (P3.00); also elsewhere on the board
GND: C201.2, C210.2, J201.5 (GND), J202.3 (GND1), J202.5 (GND2), TP203.1, U201.1 (GND), U201.3 (GND3), U201.10 (GND10), U201.11 (GND11), U201.20 (GND20), U201.D0 (GND_D0), U201.E0 (GND_E0), U201.F0 (GND_F0); also elsewhere on the board
GNSS_EXTINT: U201.C6 (P1.08); also elsewhere on the board
GNSS_RESET_N: U201.A6 (P1.06); also elsewhere on the board
GNSS_RX: U201.C7 (P1.05); also elsewhere on the board
GNSS_TIMEPULSE: U201.D6 (P1.09); also elsewhere on the board
GNSS_TX: U201.A8 (P1.04); also elsewhere on the board
IMU_INT: U201.E3 (P1.10); also elsewhere on the board
KEY_C: U201.F6 (P1.27); also elsewhere on the board
KEY_L: U201.12 (P1.26); also elsewhere on the board
KEY_R: U201.A9 (P1.30); also elsewhere on the board
MOD_RESET: J201.3 (RESET), J202.10 (nRESET), U201.4 (RESET)
NOR_CS: U201.D8 (P2.05); also elsewhere on the board
NOR_MISO: U201.C8 (P2.04); also elsewhere on the board
NOR_MOSI: R507.1, U201.D9 (P2.02)
NOR_MOSI_F: R507.2; also elsewhere on the board
NOR_SCK: R506.1, U201.E9 (P2.01)
NOR_SCK_F: R506.2; also elsewhere on the board
PMIC_INT: U201.A2 (P0.00); also elsewhere on the board
PWR_SCL: R108.2, U201.B1 (P0.03); also elsewhere on the board
PWR_SDA: R107.2, U201.B0 (P0.02); also elsewhere on the board
RGB_B: U201.E4 (P1.22); also elsewhere on the board
RGB_G: U201.14 (P1.19); also elsewhere on the board
RGB_R: U201.17 (P1.16); also elsewhere on the board
SENS_SCL: R505.2, U201.B8 (P1.03); also elsewhere on the board
SENS_SDA: R504.2, U201.B9 (P1.29); also elsewhere on the board
SWDCLK: J201.4 (SWDCLK), J202.4 (SWDCLK), U201.6 (SWDCLK)
SWDIO: J201.2 (SWDIO), J202.2 (SWDIO), U201.5 (SWDIO)
USB_DM: U201.7 (USB_DM); also elsewhere on the board
USB_DP: U201.8 (USB_DP); also elsewhere on the board
VBUSOUT: U201.9 (VBUS); also elsewhere on the board

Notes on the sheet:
Modulo ME54BS13 (nRF54LM20A)
Depuracao SWD e console
2 MCU e depuracao - 15 posicoes. NADA MONTADO NEM MEDIDO.

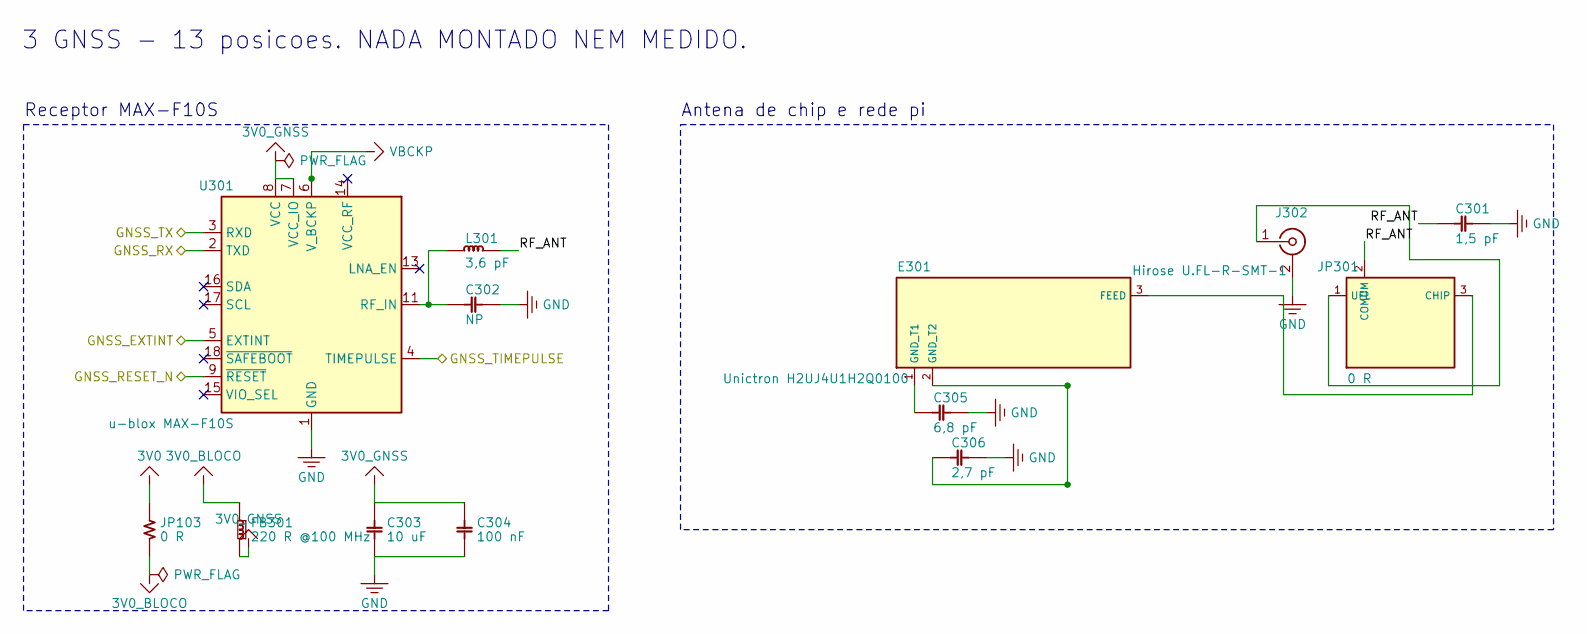
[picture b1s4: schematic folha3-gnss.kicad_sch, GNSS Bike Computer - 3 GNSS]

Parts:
C301: 1,5 pF; C_0402_1005Metric
C302: NP; C_0402_1005Metric
C303: 10 uF; C_0603_1608Metric
C304: 100 nF; C_0402_1005Metric
C305: 6,8 pF; R_0402_1005Metric
C306: 2,7 pF; R_0402_1005Metric
E301: Unictron H2UJ4U1H2Q0100; Antena_Unictron_H2UJ4U1H2Q0100_5x3mm
FB301: 220 R @100 MHz; L_0603_1608Metric
J302: Hirose U.FL-R-SMT-1; U.FL_Hirose_U.FL-R-SMT-1_Vertical
JP103: 0 R; R_0402_1005Metric
JP301: 0 R; JumperRF_3x0402
L301: 3,6 pF; L_0402_1005Metric
U301: u-blox MAX-F10S; u-blox_MAX_LCC-18_9.7x10.1mm

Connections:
3V0: JP103.1; also elsewhere on the board
3V0_BLOCO: FB301.1, JP103.2
3V0_GNSS: C303.1, C304.1, FB301.2, U301.7 (VCC_IO), U301.8 (VCC)
ANT_T1: C305.1, E301.1 (GND_T1)
ANT_T2: C306.1, E301.2 (GND_T2)
GND: C301.2, C302.2, C303.2, C304.2, C305.2, C306.2, J302.2 (Ext), U301.1 (GND), U301.10 (GND), U301.12 (GND); also elsewhere on the board
GNSS_EXTINT: U301.5 (EXTINT); also elsewhere on the board
GNSS_RESET_N: U301.9 (~RESET); also elsewhere on the board
GNSS_RX: U301.2 (TXD); also elsewhere on the board
GNSS_TIMEPULSE: U301.4 (TIMEPULSE); also elsewhere on the board
GNSS_TX: U301.3 (RXD); also elsewhere on the board
RF_ANT: C301.1, JP301.2 (COMUM), L301.1
RF_CHIP: E301.3 (FEED), JP301.3 (CHIP)
RF_IN: C302.1, L301.2, U301.11 (RF_IN)
RF_UFL: J302.1 (In), JP301.1 (UFL)
VBCKP: U301.6 (V_BCKP); also elsewhere on the board

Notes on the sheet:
Receptor MAX-F10S
Antena de chip e rede pi
3 GNSS - 13 posicoes. NADA MONTADO NEM MEDIDO.

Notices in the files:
README.md:
- **Este projeto é CC BY-NC 4.0** ([`LICENSE`](LICENSE), decisão do dono em 2026-09-26): código, hardware e documentação podem ser copiados, estudados, modificados e redistribuídos, com atribuição, e **não podem ser usados comercialmente**.
